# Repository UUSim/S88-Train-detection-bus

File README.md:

# S88-Train-detection-bus
PCB designs for an S88 bus for detecting model trains on a track. The Marklin S88 bus is based on a shift register. More information on the Marklin S88 bus can be found here:
* [S88-N - s88 over RJ45](http://www.s88-n.eu/index-en.html) (English)
* [Digital Bahn.de](https://www.digital-bahn.de/info_tech/s88.htm) (Deutsch)
* [Marklin S88 Link](http://www.maerklin.de/en/products/details/article/60883/) ([PDF manual](https://static.maerklin.de/damcontent/d1/65/d1652564aaf7fea4ec6f6f887203d2681464362779.pdf)) (English/Deutsch)
* [Avontuur in miniatuur - Terugmelding](http://www.floodland.nl/aim/info_terugmelding_1.htm) (Nederlands)

This design uses master and slave boards, connected to a single bus controller (e.g. a Marklin CS or an Arduino). Both boards are suitable for DIY-etching (master: uv-lighting, slave: toner-tranfer). The number of drilling-holes is kept to a minimum. **Note: there is no hysteresis on the inputs. This must be implemented in the controller software.**
## Master board
The master board uses 3 74hc165 ICs, resulting in 24 inputs. The master boards can be chained together. Each connector on the master board serves a group of 3 inputs, which are connected via a slave board. All inputs are fitted with pullups. The train wheels connect the inputs to ground when entering a track section.

[See the InputModule for the design files of the master board](InputModule/README.md)

## Slave board
A small slave board can be mounted close to the tracks, and connects up to 3 track segments. The board features a led for diagnostic purposes.  

## Video of result
[!](https://www.youtube.com/watch?v=ed31EqeW7o0)

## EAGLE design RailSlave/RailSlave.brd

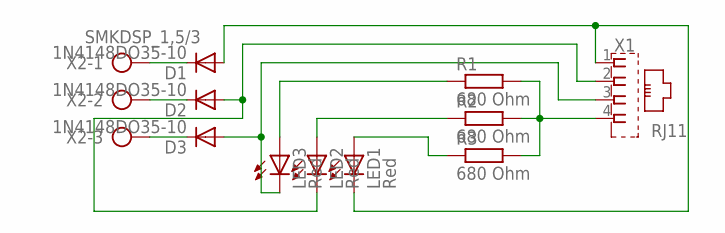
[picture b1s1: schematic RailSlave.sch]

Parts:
D1, D2, D3: 1N4148DO35-10; DO35-10
LED1, LED2, LED3: Red; LED3MM
R1, R2, R3: 680 Ohm; 0207/10
X1: RJ11; RJ116PC4
X2: SMKDSP_1,5/3

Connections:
unnamed: D2.C, X2.2
unnamed: D1.C, X2.1
unnamed: D3.C, X2.3
unnamed: D1.A, LED1.K (C), X1.1
unnamed: D2.A, LED2.K (C), X1.2
unnamed: R1.2, R2.2, R3.2, X1.4
unnamed: LED3.A, R1.1
unnamed: LED2.A, R2.1
unnamed: D3.A, LED3.K (C), X1.3
unnamed: LED1.A, R3.1

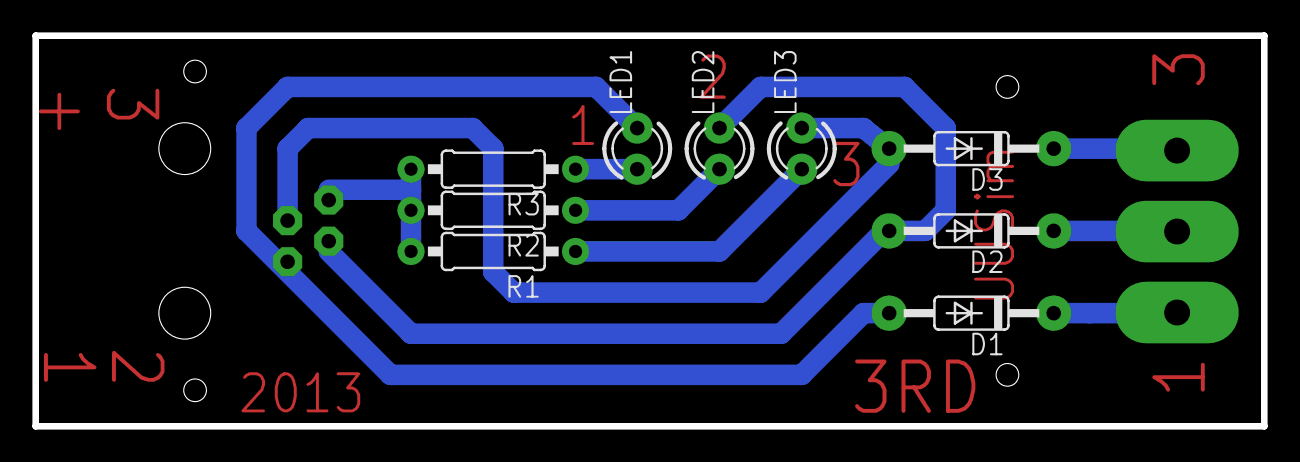
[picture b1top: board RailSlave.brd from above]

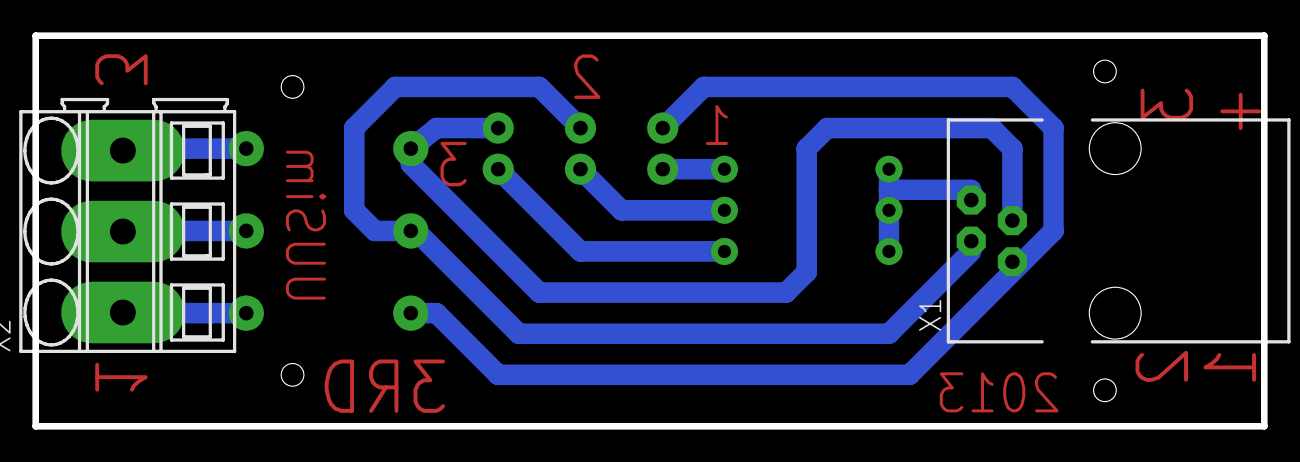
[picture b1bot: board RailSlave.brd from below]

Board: 2 copper layers, 75.9 x 24.1 mm, 11 parts (2 on the bottom side), 10 nets.

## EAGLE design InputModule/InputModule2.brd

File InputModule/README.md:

# InputModule
PCB designs of the Input module of the S88 train detection bus. This is the master board. It uses 3 74hc165 ICs, resulting in 24 inputs. The master boards can be chained together via RJ45 connectors. Each RJ11 connector on the master board serves a group of 3 inputs, which are connected via a slave board.

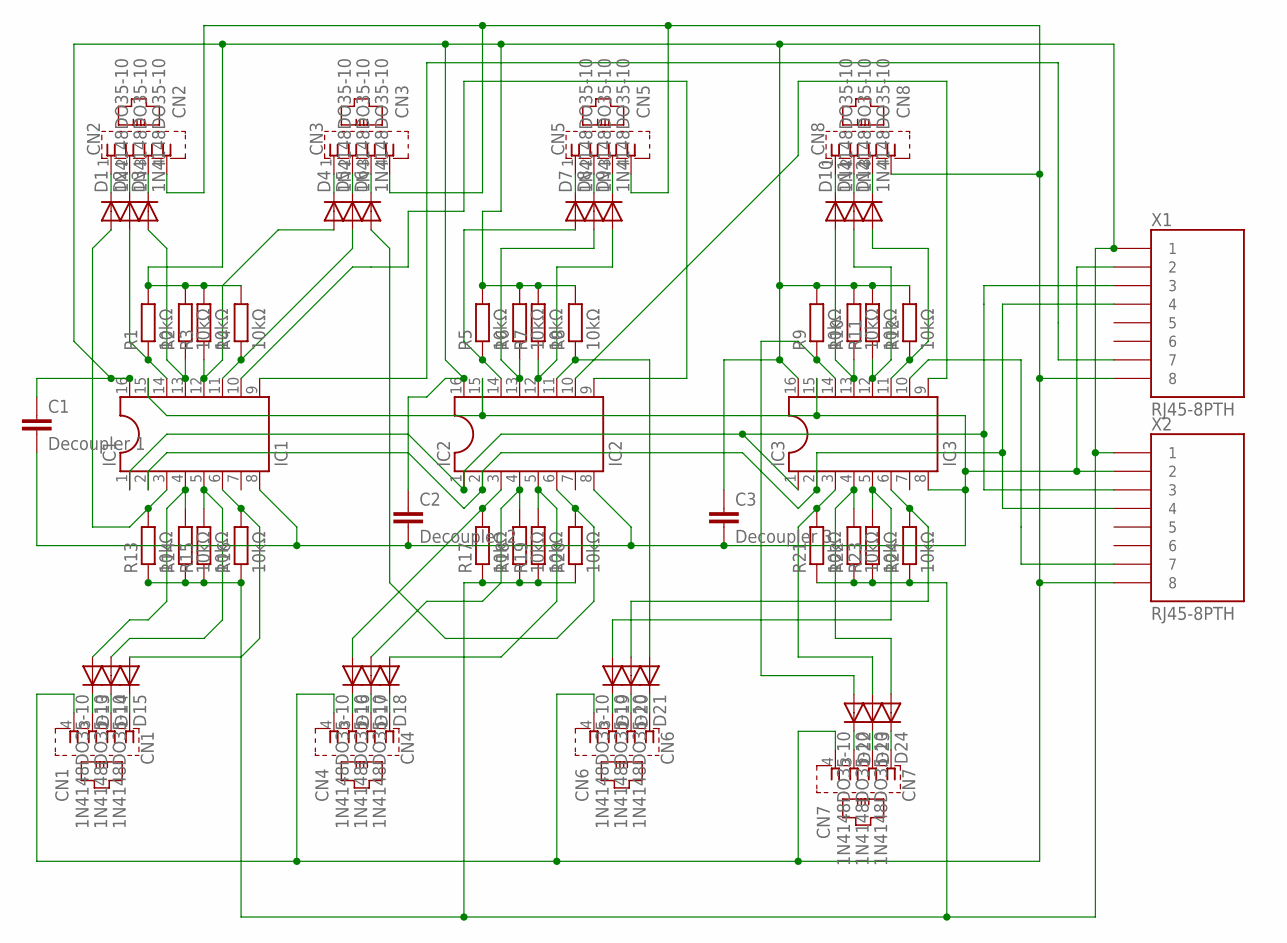
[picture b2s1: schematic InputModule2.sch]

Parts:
C1: Decoupler 1; C5B2.5
C2: Decoupler 2; C5B2.5
C3: Decoupler 3; C5B2.5
CN1: CN1; RJ116PC4
CN2: CN2; RJ116PC4
CN3: CN3; RJ116PC4
CN4: CN4; RJ116PC4
CN5: CN5; RJ116PC4
CN6: CN6; RJ116PC4
CN7: CN7; RJ116PC4
CN8: CN8; RJ116PC4
D1, D2, D3, D4, D5, D6, D7, D8, D9, D10, D11, D12, D13, D14, D15, D16, D17, D18, D19, D20, D21, D22, D23, D24: 1N4148DO35-10; DO35-10
IC1: IC1; SOCKET-16
IC2: IC2; SOCKET-16
IC3: IC3; SOCKET-16
R1, R2, R3, R4, R5, R6, R7, R8, R9, R10, R11, R12, R13, R14, R15, R16, R17, R18, R19, R20, R21, R22, R23, R24: 10kΩ; 0207/10
X1, X2: RJ45-8PTH; RJ45-8

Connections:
3RD_DEBUG: CN1.4, CN2.4, CN3.4, CN4.4, CN5.4, CN6.4, CN7.4, CN8.4, X1.8, X2.8
GND: C1.2, C2.2, C3.2, IC1.8, IC1.15, IC2.8, IC2.15, IC3.8, IC3.15, X1.2, X2.2
unnamed: CN8.2, D11.C
unnamed: CN5.2, D8.C
unnamed: CN8.1, D10.C
unnamed: CN8.3, D12.C
unnamed: CN7.1, D24.C
unnamed: CN2.2, D2.C
unnamed: CN3.1, D4.C
unnamed: CN7.2, D23.C
unnamed: CN1.3, D13.C
unnamed: CN6.2, D20.C
unnamed: CN7.3, D22.C
unnamed: CN6.1, D21.C
unnamed: CN2.1, D1.C
unnamed: CN2.3, D3.C
unnamed: CN3.2, D5.C
unnamed: CN3.3, D6.C
unnamed: CN5.1, D7.C
unnamed: CN5.3, D9.C
unnamed: CN6.3, D19.C
unnamed: CN4.2, D17.C
unnamed: CN4.1, D18.C
unnamed: CN4.3, D16.C
unnamed: CN1.2, D14.C
unnamed: CN1.1, D15.C
unnamed: D13.A, IC1.4, R14.2
unnamed: D1.A, IC1.3, R13.2
unnamed: D14.A, IC1.5, R15.2
unnamed: D12.A, IC3.11, R12.1
unnamed: D24.A, IC3.4, R22.2
unnamed: D20.A, IC3.6, R24.2
unnamed: D2.A, IC1.14, R1.1
unnamed: D3.A, IC1.13, R2.1
unnamed: D4.A, IC1.12, R3.1
unnamed: D5.A, IC1.11, R4.1
unnamed: D7.A, IC2.14, R5.1
unnamed: D8.A, IC2.13, R6.1
unnamed: D9.A, IC2.12, R7.1
unnamed: D21.A, IC2.11, R8.1
unnamed: D15.A, IC1.6, R16.2
unnamed: D10.A, IC3.13, R10.1
unnamed: D17.A, IC2.4, R18.2
unnamed: D16.A, IC2.3, R17.2
unnamed: D18.A, IC2.5, R19.2
unnamed: D6.A, IC2.6, R20.2
unnamed: D19.A, IC3.5, R23.2
unnamed: D23.A, IC3.3, R21.2
unnamed: D11.A, IC3.12, R11.1
unnamed: D22.A, IC3.14, R9.1
unnamed: IC1.1, IC2.1, IC3.1, X1.3, X2.3
unnamed: IC1.2, IC2.2, IC3.2, X1.4, X2.4
unnamed: IC1.10, IC2.9
unnamed: IC2.10, IC3.9
unnamed: IC1.9, X1.7
unnamed: IC3.10, X2.7
VCC: C1.1, C2.1, C3.1, IC1.16, IC2.16, IC3.16, R1.2, R2.2, R3.2, R4.2, R5.2, R6.2, R7.2, R8.2, R9.2, R10.2, R11.2, R12.2, R13.1, R14.1, R15.1, R16.1, R17.1, R18.1, R19.1, R20.1, R21.1, R22.1, R23.1, R24.1, X1.1, X2.1

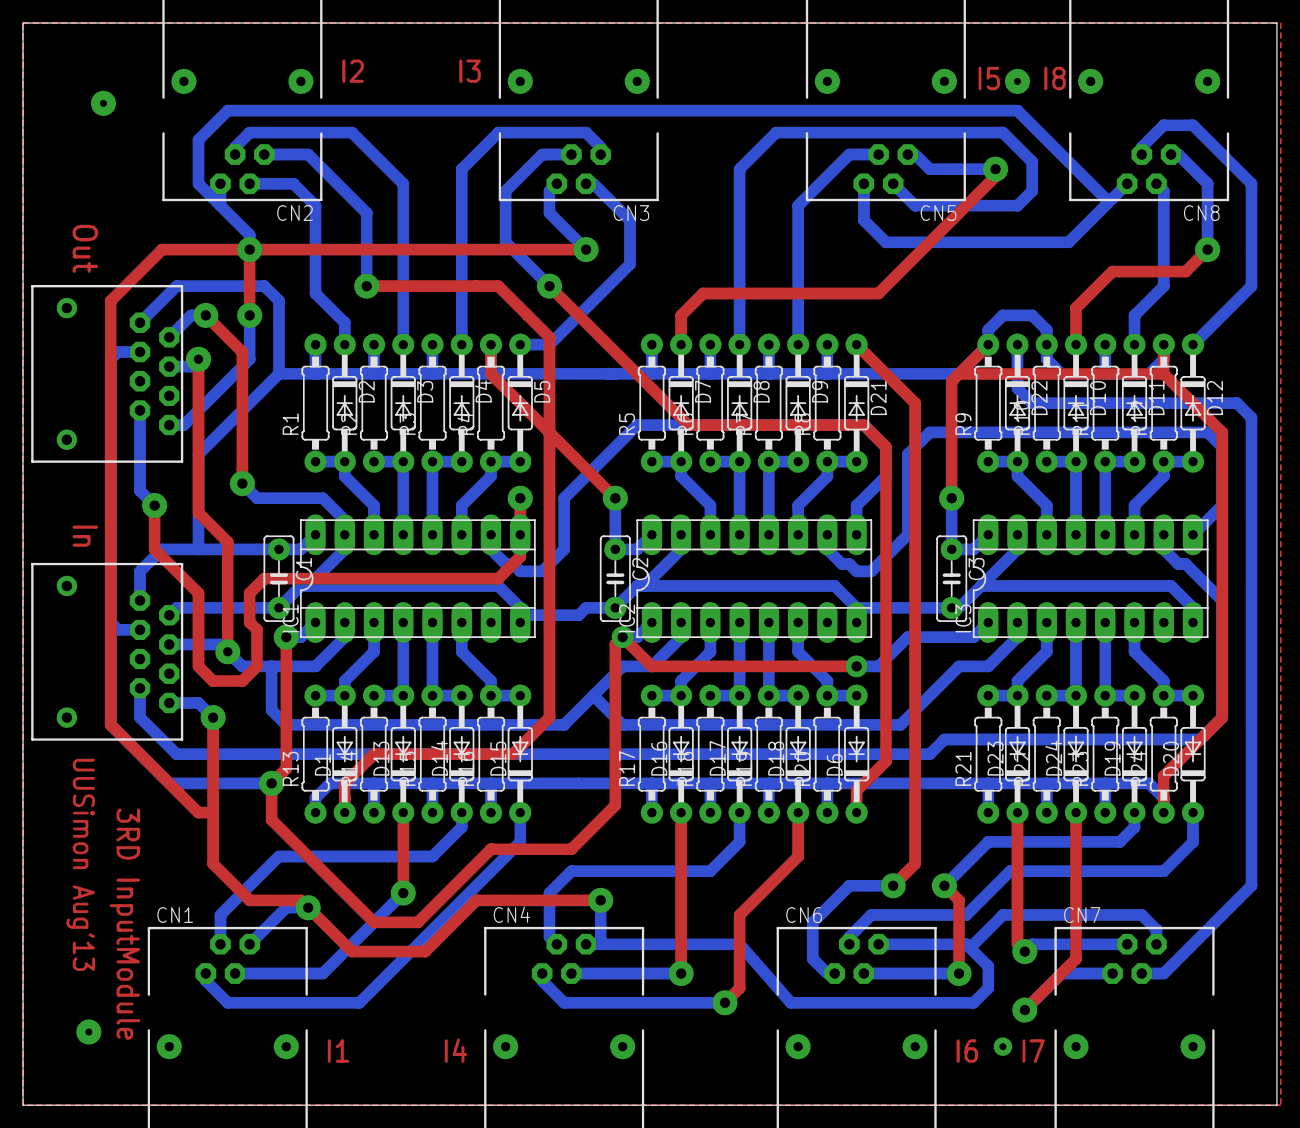
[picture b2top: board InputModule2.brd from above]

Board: 2 copper layers, 108.9 x 94.0 mm, 64 parts (0 on the bottom side), 57 nets.

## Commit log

2017-01-20 Added pictures of result
    Also includes breadboard schematic of s88 bus with shift registers
2017-01-20 Updated readme
    Added description and pictures to readme
2017-01-23 Added Eagle design files for the master board. Added readme with screenshot.
2017-01-23 Linked master board design files in readme
2017-01-25 Updated readme with links to S88 bus specifications. Added design files of the slave board.

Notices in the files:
parts and their libraries:
SparkFun-Connectors: Licensing: CC v3.0 Share-Alike You are welcome to use this library for commercial purposes.
